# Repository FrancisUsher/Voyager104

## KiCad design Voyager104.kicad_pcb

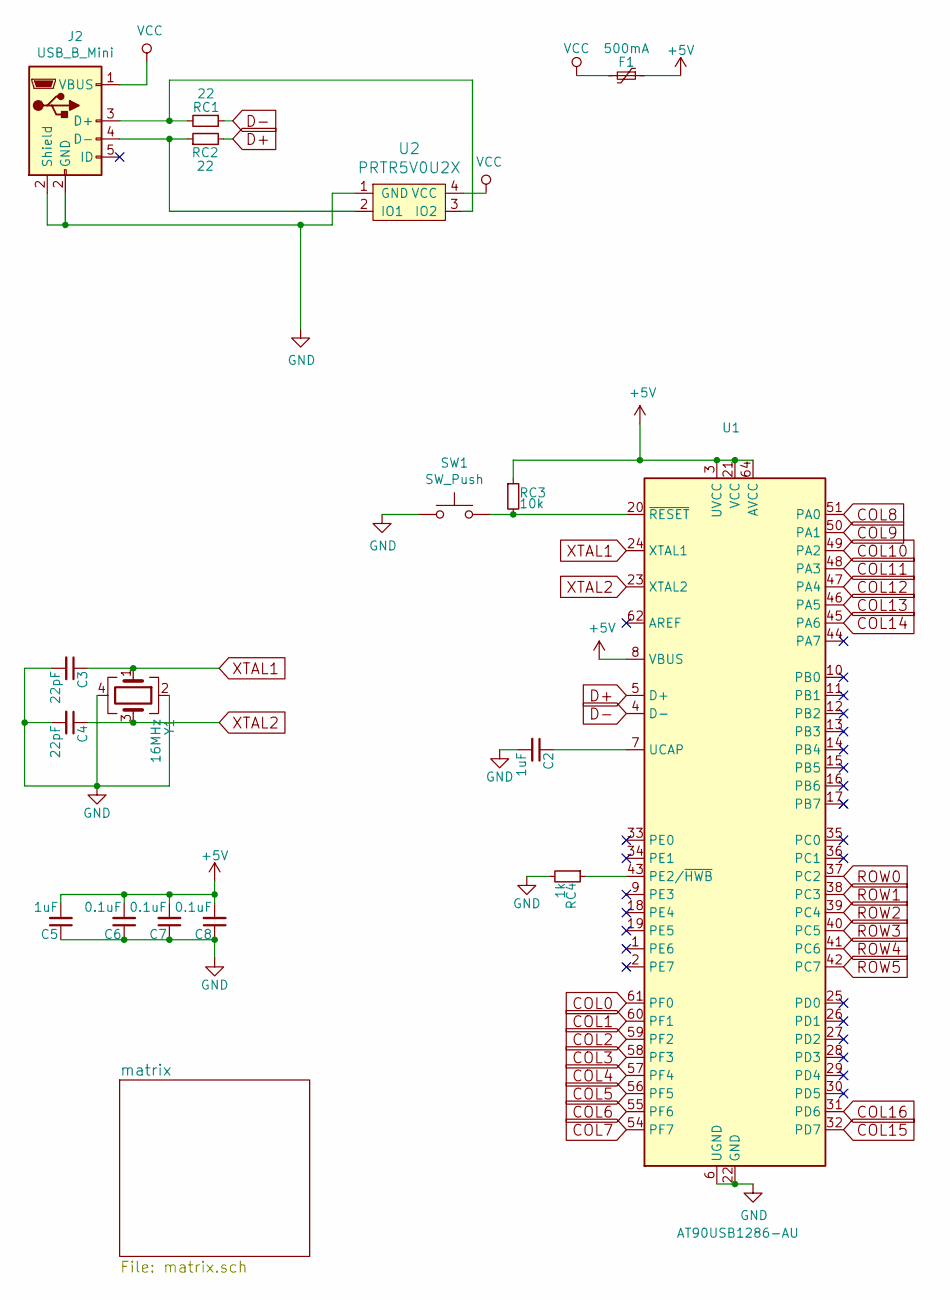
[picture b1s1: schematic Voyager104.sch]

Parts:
C2, C5: 1uF; C_0603
C3, C4: 22pF; C_0603
C6, C7, C8: 0.1uF; C_0603
F1: 500mA; Fuse_SMD1206_Reflow
J2: USB_B_Mini; JST_PH_S5B-PH-SM4-TB_05x2.00mm_Angled
RC1, RC2: 22; R_0603
RC3: 10k; R_0603
RC4: 1k; R_0603
SW1: SW_Push; SKQG-1155865
U1: AT90USB1286-AU; QFN-64-1EP_9x9mm_Pitch0.5mm
U2: PRTR5V0U2X; SOT143B
Y1: 16MHz; Crystal_SMD_3225-4pin_3.2x2.5mm

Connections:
+5V: C5.2, C6.2, C7.2, C8.2, F1.1, RC3.1, U1.3 (UVCC), U1.8 (VBUS), U1.21 (VCC), U1.52 (VCC), U1.64 (AVCC)
COL0: U1.61 (PF0); also elsewhere on the board
COL1: U1.60 (PF1); also elsewhere on the board
COL2: U1.59 (PF2); also elsewhere on the board
COL3: U1.58 (PF3); also elsewhere on the board
COL4: U1.57 (PF4); also elsewhere on the board
COL5: U1.56 (PF5); also elsewhere on the board
COL6: U1.55 (PF6); also elsewhere on the board
COL7: U1.54 (PF7); also elsewhere on the board
COL8: U1.51 (PA0); also elsewhere on the board
COL9: U1.50 (PA1); also elsewhere on the board
COL10: U1.49 (PA2); also elsewhere on the board
COL11: U1.48 (PA3); also elsewhere on the board
COL12: U1.47 (PA4); also elsewhere on the board
COL13: U1.46 (PA5); also elsewhere on the board
COL14: U1.45 (PA6); also elsewhere on the board
COL15: U1.32 (PD7); also elsewhere on the board
COL16: U1.31 (PD6); also elsewhere on the board
D+: RC2.2, U1.5 (D+)
D-: RC1.1, U1.4 (D-)
GND: C2.2, C3.2, C4.2, C5.1, C6.1, C7.1, C8.1, J2.2 (GND), RC4.2, SW1.1, U1.6 (UGND), U1.22 (GND), U1.53 (GND), U1.63 (GND), U1.65 (GND), U2.1 (GND), Y1.2, Y1.4
unnamed: C2.1, U1.7 (UCAP)
unnamed: J2.3 (D+), RC1.2, U2.3 (IO2)
unnamed: J2.4 (D-), RC2.1, U2.2 (IO1)
unnamed: RC3.2, SW1.2, U1.20 (~RESET)
unnamed: RC4.1, U1.43 (PE2/~HWB)
ROW0: U1.37 (PC2); also elsewhere on the board
ROW1: U1.38 (PC3); also elsewhere on the board
ROW2: U1.39 (PC4); also elsewhere on the board
ROW3: U1.40 (PC5); also elsewhere on the board
ROW4: U1.41 (PC6); also elsewhere on the board
ROW5: U1.42 (PC7); also elsewhere on the board
VCC: F1.2, J2.1 (VBUS), U2.4 (VCC)
XTAL1: C3.1, U1.24 (XTAL1), Y1.1
XTAL2: C4.1, U1.23 (XTAL2), Y1.3

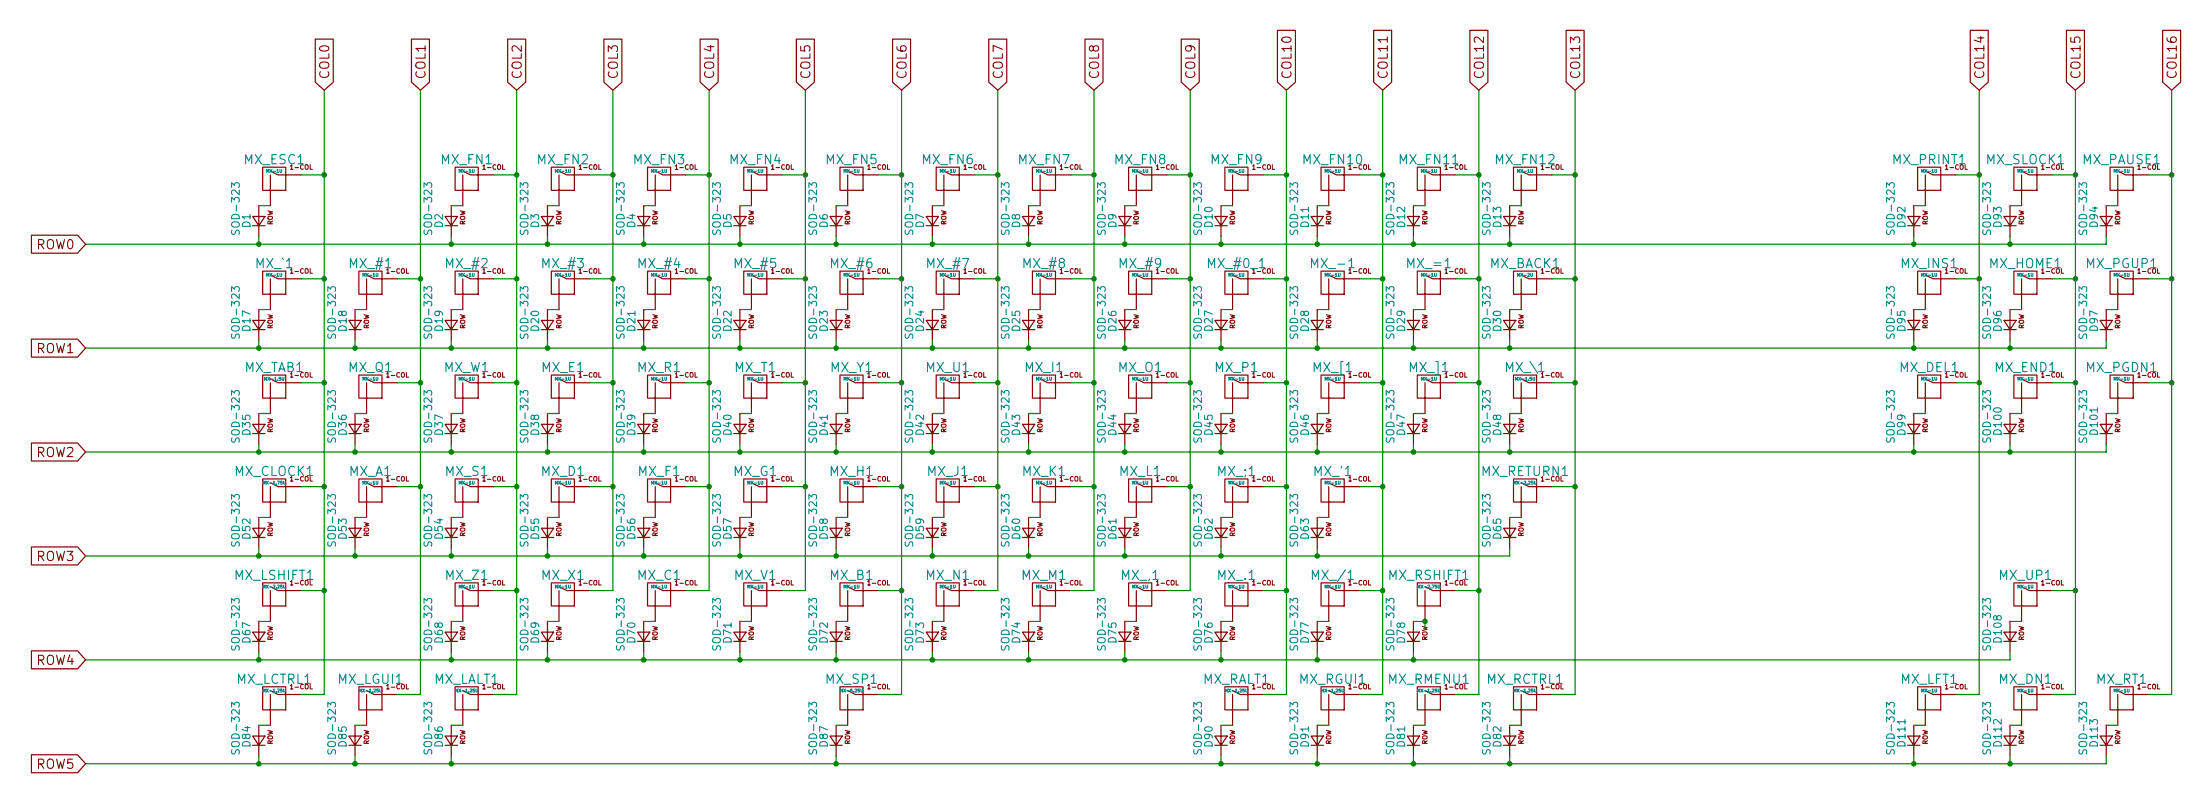
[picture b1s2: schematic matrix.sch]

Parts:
D1, D2, D3, D4, D5, D6, D7, D8, D9, D10, D11, D12, D13, D17, D18, D19, D20, D21, D22, D23, D24, D25, D26, D27, D28, D29, D30, D35, D36, D37, D38, D39, D40, D41, D42, D43, D44, D45, D46, D47, D48, D52, D53, D54, D55, D56, D57, D58, D59, D60, D61, D62, D63, D65, D67, D68, D69, D70, D71, D72, D73, D74, D75, D76, D77, D78, D81, D82, D84, D85, D86, D87, D90, D91, D92, D93, D94, D95, D96, D97, D99, D100, D101, D108, D111, D112, D113: SOD-323; D_SOD-123
MX_#0_1, MX_#1, MX_#2, MX_#3, MX_#4, MX_#5, MX_#6, MX_#7, MX_#8, MX_#9: MX-1U; SW_Cherry_MX1A_1.00u_PCB
MX_'1: MX-1U; SW_Cherry_MX1A_1.00u_PCB
MX_,1: MX-1U; SW_Cherry_MX1A_1.00u_PCB
MX_-1: MX-1U; SW_Cherry_MX1A_1.00u_PCB
MX_.1: MX-1U; SW_Cherry_MX1A_1.00u_PCB
MX_/1: MX-1U; SW_Cherry_MX1A_1.00u_PCB
MX_;1: MX-1U; SW_Cherry_MX1A_1.00u_PCB
MX_=1: MX-1U; SW_Cherry_MX1A_1.00u_PCB
MX_A1: MX-1U; SW_Cherry_MX1A_1.00u_PCB
MX_B1: MX-1U; SW_Cherry_MX1A_1.00u_PCB
MX_BACK1: MX-2U; SW_Cherry_MX1A_2.00u_PCB
MX_C1: MX-1U; SW_Cherry_MX1A_1.00u_PCB
MX_CLOCK1: MX-1.75U; SW_Cherry_MX1A_1.75u_PCB
MX_D1: MX-1U; SW_Cherry_MX1A_1.00u_PCB
MX_DEL1: MX-1U; SW_Cherry_MX1A_1.00u_PCB
MX_DN1: MX-1U; SW_Cherry_MX1A_1.00u_PCB
MX_E1: MX-1U; SW_Cherry_MX1A_1.00u_PCB
MX_END1: MX-1U; SW_Cherry_MX1A_1.00u_PCB
MX_ESC1: MX-1U; SW_Cherry_MX1A_1.00u_PCB
MX_F1: MX-1U; SW_Cherry_MX1A_1.00u_PCB
MX_FN1, MX_FN2, MX_FN3, MX_FN4, MX_FN5, MX_FN6, MX_FN7, MX_FN8, MX_FN9, MX_FN10, MX_FN11, MX_FN12: MX-1U; SW_Cherry_MX1A_1.00u_PCB
MX_G1: MX-1U; SW_Cherry_MX1A_1.00u_PCB
MX_H1: MX-1U; SW_Cherry_MX1A_1.00u_PCB
MX_HOME1: MX-1U; SW_Cherry_MX1A_1.00u_PCB
MX_I1: MX-1U; SW_Cherry_MX1A_1.00u_PCB
MX_INS1: MX-1U; SW_Cherry_MX1A_1.00u_PCB
MX_J1: MX-1U; SW_Cherry_MX1A_1.00u_PCB
MX_K1: MX-1U; SW_Cherry_MX1A_1.00u_PCB
MX_L1: MX-1U; SW_Cherry_MX1A_1.00u_PCB
MX_LALT1: MX-1.25U; SW_Cherry_MX1A_1.25u_PCB
MX_LCTRL1: MX-1.25U; SW_Cherry_MX1A_1.25u_PCB
MX_LFT1: MX-1U; SW_Cherry_MX1A_1.00u_PCB
MX_LGUI1: MX-1.25U; SW_Cherry_MX1A_1.25u_PCB
MX_LSHIFT1: MX-2.25U; SW_Cherry_MX1A_2.25u_PCB
MX_M1: MX-1U; SW_Cherry_MX1A_1.00u_PCB
MX_N1: MX-1U; SW_Cherry_MX1A_1.00u_PCB
MX_O1: MX-1U; SW_Cherry_MX1A_1.00u_PCB
MX_P1: MX-1U; SW_Cherry_MX1A_1.00u_PCB
MX_PAUSE1: MX-1U; SW_Cherry_MX1A_1.00u_PCB
MX_PGDN1: MX-1U; SW_Cherry_MX1A_1.00u_PCB
MX_PGUP1: MX-1U; SW_Cherry_MX1A_1.00u_PCB
MX_PRINT1: MX-1U; SW_Cherry_MX1A_1.00u_PCB
MX_Q1: MX-1U; SW_Cherry_MX1A_1.00u_PCB
MX_R1: MX-1U; SW_Cherry_MX1A_1.00u_PCB
MX_RALT1: MX-1.25U; SW_Cherry_MX1A_1.25u_PCB
MX_RCTRL1: MX-1.25U; SW_Cherry_MX1A_1.25u_PCB
MX_RETURN1: MX-2.25U; SW_Cherry_MX1A_2.25u_PCB
MX_RGUI1: MX-1.25U; SW_Cherry_MX1A_1.25u_PCB
MX_RMENU1: MX-1.25U; SW_Cherry_MX1A_1.25u_PCB
MX_RSHIFT1: MX-2.75U; SW_Cherry_MX1A_2.75u_PCB
MX_RT1: MX-1U; SW_Cherry_MX1A_1.00u_PCB
MX_S1: MX-1U; SW_Cherry_MX1A_1.00u_PCB
MX_SLOCK1: MX-1U; SW_Cherry_MX1A_1.00u_PCB
MX_SP1: MX-6.25U; SW_Cherry_MX1A_6.25u_PCB
MX_T1: MX-1U; SW_Cherry_MX1A_1.00u_PCB
MX_TAB1: MX-1.5U; SW_Cherry_MX1A_1.50u_PCB
MX_U1: MX-1U; SW_Cherry_MX1A_1.00u_PCB
MX_UP1: MX-1U; SW_Cherry_MX1A_1.00u_PCB
MX_V1: MX-1U; SW_Cherry_MX1A_1.00u_PCB
MX_W1: MX-1U; SW_Cherry_MX1A_1.00u_PCB
MX_X1: MX-1U; SW_Cherry_MX1A_1.00u_PCB
MX_Y1: MX-1U; SW_Cherry_MX1A_1.00u_PCB
MX_Z1: MX-1U; SW_Cherry_MX1A_1.00u_PCB
MX_[1: MX-1U; SW_Cherry_MX1A_1.00u_PCB
MX_\1: MX-1.5U; SW_Cherry_MX1A_1.50u_PCB
MX_]1: MX-1U; SW_Cherry_MX1A_1.00u_PCB
MX_`1: MX-1U; SW_Cherry_MX1A_1.00u_PCB

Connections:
COL0: MX_CLOCK1.1 (COL), MX_ESC1.1 (COL), MX_LCTRL1.1 (COL), MX_LSHIFT1.1 (COL), MX_TAB1.1 (COL), MX_`1.1 (COL); also elsewhere on the board
COL1: MX_#1.1 (COL), MX_A1.1 (COL), MX_LGUI1.1 (COL), MX_Q1.1 (COL); also elsewhere on the board
COL2: MX_#2.1 (COL), MX_FN1.1 (COL), MX_LALT1.1 (COL), MX_S1.1 (COL), MX_W1.1 (COL), MX_Z1.1 (COL); also elsewhere on the board
COL3: MX_#3.1 (COL), MX_D1.1 (COL), MX_E1.1 (COL), MX_FN2.1 (COL), MX_X1.1 (COL); also elsewhere on the board
COL4: MX_#4.1 (COL), MX_C1.1 (COL), MX_F1.1 (COL), MX_FN3.1 (COL), MX_R1.1 (COL); also elsewhere on the board
COL5: MX_#5.1 (COL), MX_FN4.1 (COL), MX_G1.1 (COL), MX_T1.1 (COL), MX_V1.1 (COL); also elsewhere on the board
COL6: MX_#6.1 (COL), MX_B1.1 (COL), MX_FN5.1 (COL), MX_H1.1 (COL), MX_SP1.1 (COL), MX_Y1.1 (COL); also elsewhere on the board
COL7: MX_#7.1 (COL), MX_FN6.1 (COL), MX_J1.1 (COL), MX_N1.1 (COL), MX_U1.1 (COL); also elsewhere on the board
COL8: MX_#8.1 (COL), MX_FN7.1 (COL), MX_I1.1 (COL), MX_K1.1 (COL), MX_M1.1 (COL); also elsewhere on the board
COL9: MX_#9.1 (COL), MX_,1.1 (COL), MX_FN8.1 (COL), MX_L1.1 (COL), MX_O1.1 (COL); also elsewhere on the board
COL10: MX_#0_1.1 (COL), MX_.1.1 (COL), MX_;1.1 (COL), MX_FN9.1 (COL), MX_P1.1 (COL), MX_RALT1.1 (COL); also elsewhere on the board
COL11: MX_'1.1 (COL), MX_-1.1 (COL), MX_/1.1 (COL), MX_FN10.1 (COL), MX_RGUI1.1 (COL), MX_[1.1 (COL); also elsewhere on the board
COL12: MX_=1.1 (COL), MX_FN11.1 (COL), MX_RMENU1.1 (COL), MX_RSHIFT1.1 (COL), MX_]1.1 (COL); also elsewhere on the board
COL13: MX_BACK1.1 (COL), MX_FN12.1 (COL), MX_RCTRL1.1 (COL), MX_RETURN1.1 (COL), MX_\1.1 (COL); also elsewhere on the board
COL14: MX_DEL1.1 (COL), MX_INS1.1 (COL), MX_LFT1.1 (COL), MX_PRINT1.1 (COL); also elsewhere on the board
COL15: MX_DN1.1 (COL), MX_END1.1 (COL), MX_HOME1.1 (COL), MX_SLOCK1.1 (COL), MX_UP1.1 (COL); also elsewhere on the board
COL16: MX_PAUSE1.1 (COL), MX_PGDN1.1 (COL), MX_PGUP1.1 (COL), MX_RT1.1 (COL); also elsewhere on the board
unnamed: D1.2 (A), MX_ESC1.2 (ROW)
unnamed: D2.2 (A), MX_FN1.2 (ROW)
unnamed: D3.2 (A), MX_FN2.2 (ROW)
unnamed: D4.2 (A), MX_FN3.2 (ROW)
unnamed: D5.2 (A), MX_FN4.2 (ROW)
unnamed: D6.2 (A), MX_FN5.2 (ROW)
unnamed: D7.2 (A), MX_FN6.2 (ROW)
unnamed: D8.2 (A), MX_FN7.2 (ROW)
unnamed: D9.2 (A), MX_FN8.2 (ROW)
unnamed: D10.2 (A), MX_FN9.2 (ROW)
unnamed: D11.2 (A), MX_FN10.2 (ROW)
unnamed: D12.2 (A), MX_FN11.2 (ROW)
unnamed: D13.2 (A), MX_FN12.2 (ROW)
unnamed: D17.2 (A), MX_`1.2 (ROW)
unnamed: D18.2 (A), MX_#1.2 (ROW)
unnamed: D19.2 (A), MX_#2.2 (ROW)
unnamed: D20.2 (A), MX_#3.2 (ROW)
unnamed: D21.2 (A), MX_#4.2 (ROW)
unnamed: D22.2 (A), MX_#5.2 (ROW)
unnamed: D23.2 (A), MX_#6.2 (ROW)
unnamed: D24.2 (A), MX_#7.2 (ROW)
unnamed: D25.2 (A), MX_#8.2 (ROW)
unnamed: D26.2 (A), MX_#9.2 (ROW)
unnamed: D27.2 (A), MX_#0_1.2 (ROW)
unnamed: D28.2 (A), MX_-1.2 (ROW)
unnamed: D29.2 (A), MX_=1.2 (ROW)
unnamed: D30.2 (A), MX_BACK1.2 (ROW)
unnamed: D35.2 (A), MX_TAB1.2 (ROW)
unnamed: D36.2 (A), MX_Q1.2 (ROW)
unnamed: D37.2 (A), MX_W1.2 (ROW)
unnamed: D38.2 (A), MX_E1.2 (ROW)
unnamed: D39.2 (A), MX_R1.2 (ROW)
unnamed: D40.2 (A), MX_T1.2 (ROW)
unnamed: D41.2 (A), MX_Y1.2 (ROW)
unnamed: D42.2 (A), MX_U1.2 (ROW)
unnamed: D43.2 (A), MX_I1.2 (ROW)
unnamed: D44.2 (A), MX_O1.2 (ROW)
unnamed: D45.2 (A), MX_P1.2 (ROW)
unnamed: D46.2 (A), MX_[1.2 (ROW)
unnamed: D47.2 (A), MX_]1.2 (ROW)
unnamed: D48.2 (A), MX_\1.2 (ROW)
unnamed: D52.2 (A), MX_CLOCK1.2 (ROW)
unnamed: D53.2 (A), MX_A1.2 (ROW)
unnamed: D54.2 (A), MX_S1.2 (ROW)
unnamed: D55.2 (A), MX_D1.2 (ROW)
unnamed: D56.2 (A), MX_F1.2 (ROW)
unnamed: D57.2 (A), MX_G1.2 (ROW)
unnamed: D58.2 (A), MX_H1.2 (ROW)
unnamed: D59.2 (A), MX_J1.2 (ROW)
unnamed: D60.2 (A), MX_K1.2 (ROW)
unnamed: D61.2 (A), MX_L1.2 (ROW)
unnamed: D62.2 (A), MX_;1.2 (ROW)
unnamed: D63.2 (A), MX_'1.2 (ROW)
unnamed: D65.2 (A), MX_RETURN1.2 (ROW)
unnamed: D67.2 (A), MX_LSHIFT1.2 (ROW)
unnamed: D68.2 (A), MX_Z1.2 (ROW)
unnamed: D69.2 (A), MX_X1.2 (ROW)
unnamed: D70.2 (A), MX_C1.2 (ROW)
unnamed: D71.2 (A), MX_V1.2 (ROW)
unnamed: D72.2 (A), MX_B1.2 (ROW)
unnamed: D73.2 (A), MX_N1.2 (ROW)
unnamed: D74.2 (A), MX_M1.2 (ROW)
unnamed: D75.2 (A), MX_,1.2 (ROW)
unnamed: D76.2 (A), MX_.1.2 (ROW)
unnamed: D77.2 (A), MX_/1.2 (ROW)
unnamed: D78.2 (A), MX_RSHIFT1.2 (ROW)
unnamed: D81.2 (A), MX_RMENU1.2 (ROW)
unnamed: D82.2 (A), MX_RCTRL1.2 (ROW)
unnamed: D84.2 (A), MX_LCTRL1.2 (ROW)
unnamed: D85.2 (A), MX_LGUI1.2 (ROW)
unnamed: D86.2 (A), MX_LALT1.2 (ROW)
unnamed: D87.2 (A), MX_SP1.2 (ROW)
unnamed: D90.2 (A), MX_RALT1.2 (ROW)
unnamed: D91.2 (A), MX_RGUI1.2 (ROW)
unnamed: D92.2 (A), MX_PRINT1.2 (ROW)
unnamed: D93.2 (A), MX_SLOCK1.2 (ROW)
unnamed: D94.2 (A), MX_PAUSE1.2 (ROW)
unnamed: D95.2 (A), MX_INS1.2 (ROW)
unnamed: D96.2 (A), MX_HOME1.2 (ROW)
unnamed: D97.2 (A), MX_PGUP1.2 (ROW)
unnamed: D99.2 (A), MX_DEL1.2 (ROW)
unnamed: D100.2 (A), MX_END1.2 (ROW)
unnamed: D101.2 (A), MX_PGDN1.2 (ROW)
unnamed: D108.2 (A), MX_UP1.2 (ROW)
unnamed: D111.2 (A), MX_LFT1.2 (ROW)
unnamed: D112.2 (A), MX_DN1.2 (ROW)
unnamed: D113.2 (A), MX_RT1.2 (ROW)
ROW0: D1.1 (K), D2.1 (K), D3.1 (K), D4.1 (K), D5.1 (K), D6.1 (K), D7.1 (K), D8.1 (K), D9.1 (K), D10.1 (K), D11.1 (K), D12.1 (K), D13.1 (K), D92.1 (K), D93.1 (K), D94.1 (K); also elsewhere on the board
ROW1: D17.1 (K), D18.1 (K), D19.1 (K), D20.1 (K), D21.1 (K), D22.1 (K), D23.1 (K), D24.1 (K), D25.1 (K), D26.1 (K), D27.1 (K), D28.1 (K), D29.1 (K), D30.1 (K), D95.1 (K), D96.1 (K), D97.1 (K); also elsewhere on the board
ROW2: D35.1 (K), D36.1 (K), D37.1 (K), D38.1 (K), D39.1 (K), D40.1 (K), D41.1 (K), D42.1 (K), D43.1 (K), D44.1 (K), D45.1 (K), D46.1 (K), D47.1 (K), D48.1 (K), D99.1 (K), D100.1 (K), D101.1 (K); also elsewhere on the board
ROW3: D52.1 (K), D53.1 (K), D54.1 (K), D55.1 (K), D56.1 (K), D57.1 (K), D58.1 (K), D59.1 (K), D60.1 (K), D61.1 (K), D62.1 (K), D63.1 (K), D65.1 (K); also elsewhere on the board
ROW4: D67.1 (K), D68.1 (K), D69.1 (K), D70.1 (K), D71.1 (K), D72.1 (K), D73.1 (K), D74.1 (K), D75.1 (K), D76.1 (K), D77.1 (K), D78.1 (K), D108.1 (K); also elsewhere on the board
ROW5: D81.1 (K), D82.1 (K), D84.1 (K), D85.1 (K), D86.1 (K), D87.1 (K), D90.1 (K), D91.1 (K), D111.1 (K), D112.1 (K), D113.1 (K); also elsewhere on the board

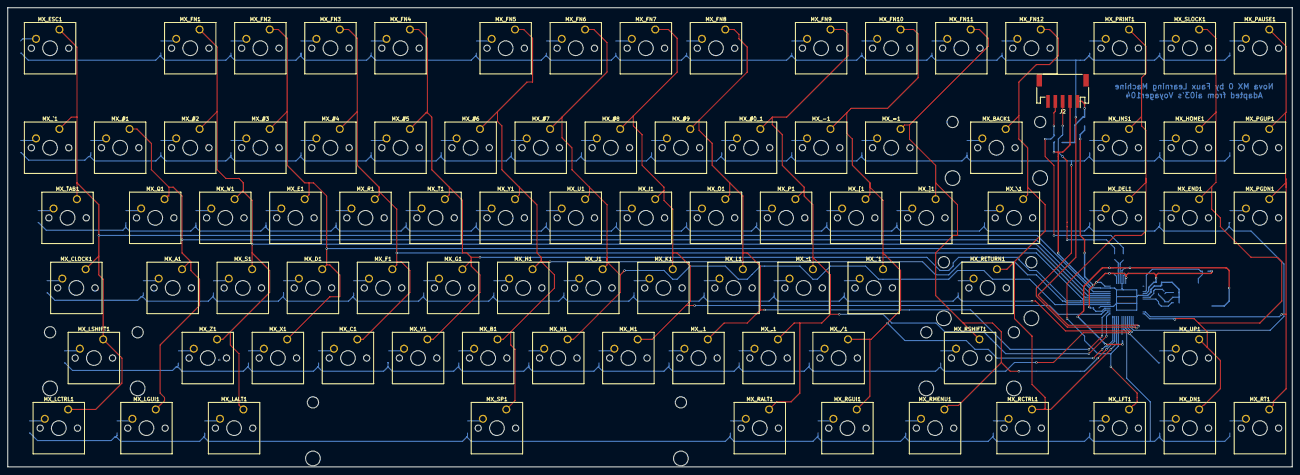
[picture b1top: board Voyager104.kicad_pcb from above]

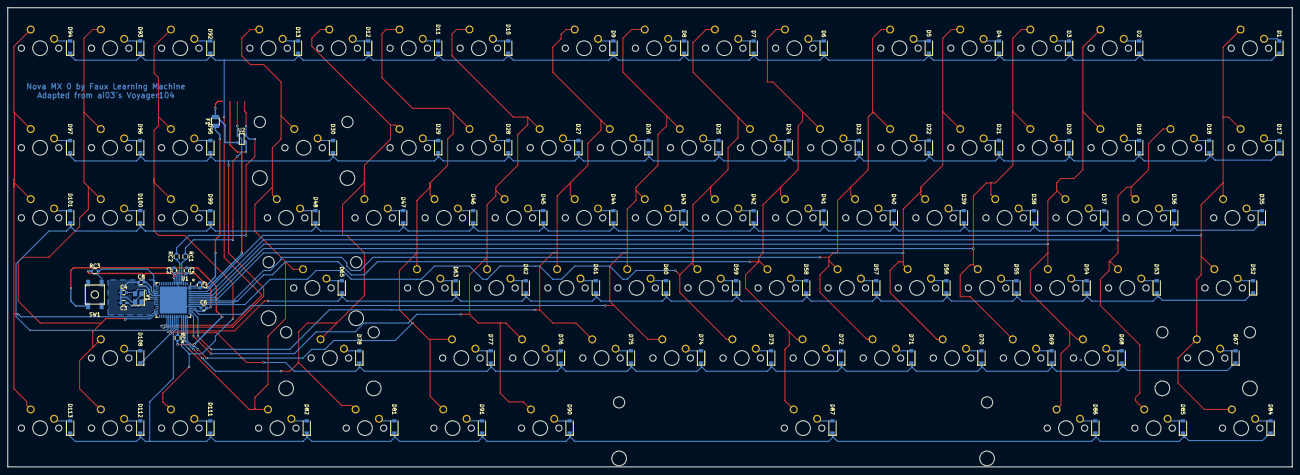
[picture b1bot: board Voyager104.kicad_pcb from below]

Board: 2 copper layers, 349.1 x 124.8 mm, 191 parts (103 on the bottom side), 122 nets.

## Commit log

2019-03-27 Simplify layout, remove LEDs and alps support, and start revising footprint positioning.
2019-03-31 Revise pcb futher.
2019-08-21 Initial revision for as yet unnamed project.
